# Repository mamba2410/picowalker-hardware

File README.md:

# picowalker hardware

This is the PCB hardware side of the [picowalker](https://github.com/mamba2410/picowalker) project.
The goal of the picowalker project is to create a new, modern equivalent to the Pokewalker distributed with the Pokemon HeartGold and SoulSilver games back in 2010.
Since those units are no longer sold and are getting harder and harder to obtain, creating a new version sounds like the easiest option. And the most fun.

The hardware is designed around the RP2350 chip. STM32U5 versions have been considered for longer battery life, but they're more expensive and I'm worried about availability (and the name "picowalker" wouldn't work!)

Software for this can be found in the [picowalker](https://github.com/mamba2410/picowalker/) and [picowalker-core](https://github.com/mamba2410/picowalker-core/) repos.

## Features

- RP2350A as the main microcontroller.
- 1.8" AMOLED screen DO0180FMST03, 448x368 resolution (running at 384x256 for 4x upscaling) driven by PIO'd QSPI (output only).
- Rechargeable lithum battery via USB-C using the BQ25628E PMIC.
- Larger form factor to accommodate larger screen and battery.
- Custom shell based on the original Pokewalker designed by Kamp.
- IrDA driven by PIO courtesy of Dmitry gr's PIO code.
- 64kB EEPROM using the M95512 chip (same as in the original walker).
- Code and extra image flash using 16MB W25Q128.
- Accelerometer with BMA400 (successor to the original Pokewalker's one).
- USB 1.1 connection for flexible communications.
- High accuracy, low power 32.768 kHz clock for more accurate timekeeping (100 PPM).

## Dependencies

- [KiCad](https://www.kicad.org/) V9.0+
- [KiKit](https://yaqwsx.github.io/KiKit/latest/installation/intro/) plugin to generate panels.
- Symbols, footprints and models are either in KiCad standard library or in a project library.

## Current state (updated 2025-12-19)

V0.4 has passed DRC checks. Will go through a few reviews so expect some tweaks.
Hoping that this will be the final version and, once validated, will be uplifted to V1.0.

Here's a render of the board.

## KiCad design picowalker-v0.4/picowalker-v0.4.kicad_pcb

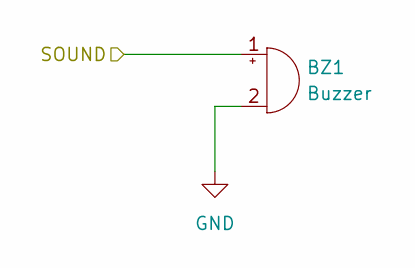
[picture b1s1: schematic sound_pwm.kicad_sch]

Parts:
BZ1: Buzzer; Huawei_P20_Speaker

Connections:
/SOUND: BZ1.1 (+); also elsewhere on the board
GND: BZ1.2 (-); also elsewhere on the board

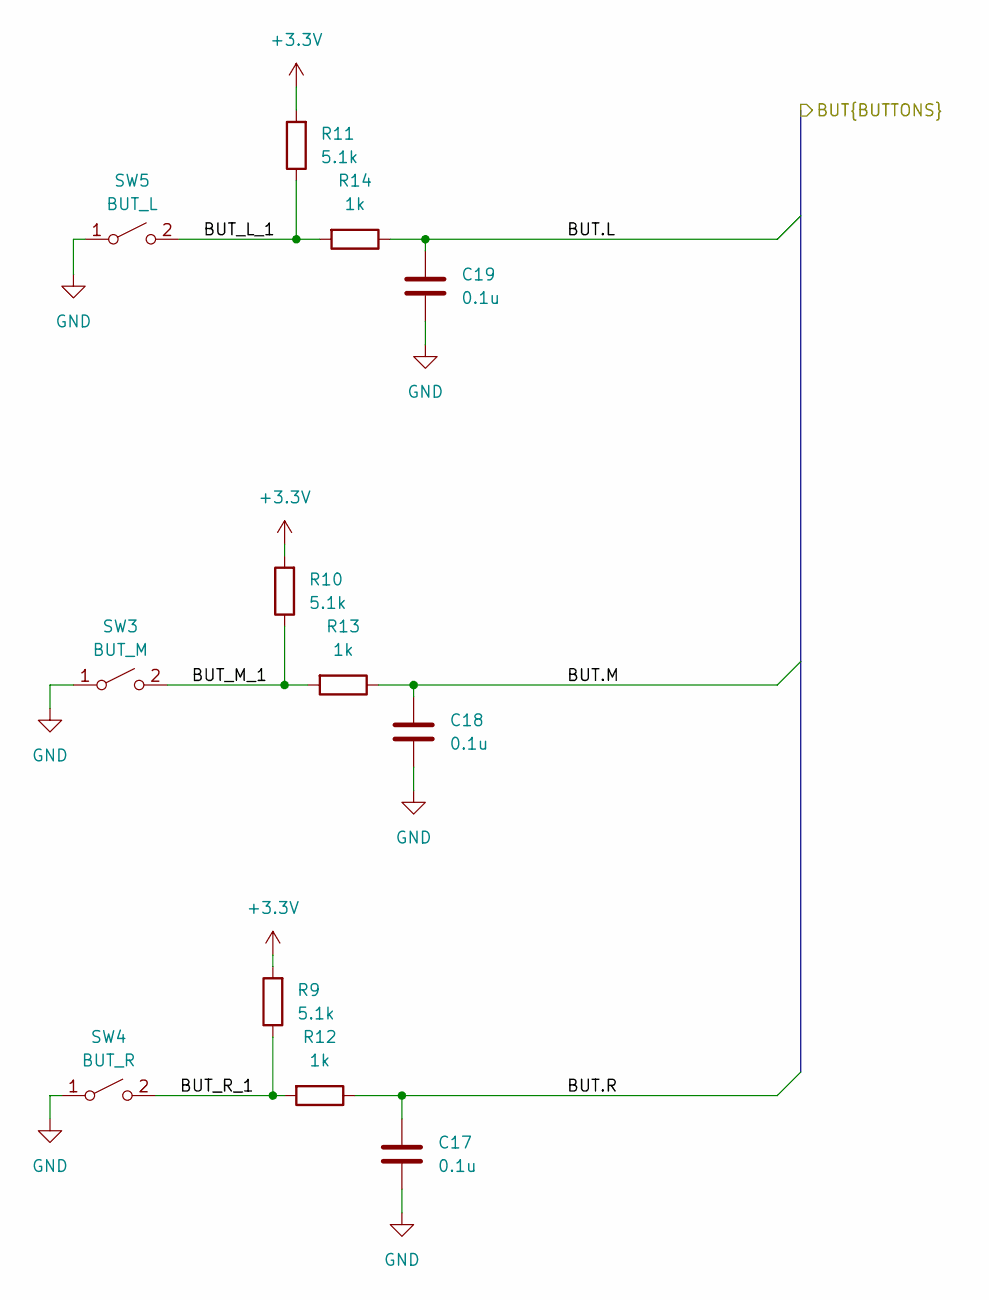
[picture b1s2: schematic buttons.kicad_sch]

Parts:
C17, C18, C19: 0.1u; C_0402_1005Metric
R9, R10, R11: 5.1k; R_0402_1005Metric
R12, R13, R14: 1k; R_0402_1005Metric
SW3: BUT_M; Button_membrane_4.2mm
SW4: BUT_R; Button_membrane_4.2mm
SW5: BUT_L; Button_membrane_4.2mm

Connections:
+3.3V: R9.2, R10.2, R11.2; also elsewhere on the board
/buttons/BUT.L: C19.1, R14.1; also elsewhere on the board
/buttons/BUT.M: C18.1, R13.1; also elsewhere on the board
/buttons/BUT.R: C17.1, R12.1; also elsewhere on the board
/buttons/BUT_L_1: R11.1, R14.2, SW5.2 (B)
/buttons/BUT_M_1: R10.1, R13.2, SW3.2 (B)
/buttons/BUT_R_1: R9.1, R12.2, SW4.2 (B)
GND: C17.2, C18.2, C19.2, SW3.1 (A), SW4.1 (A), SW5.1 (A); also elsewhere on the board

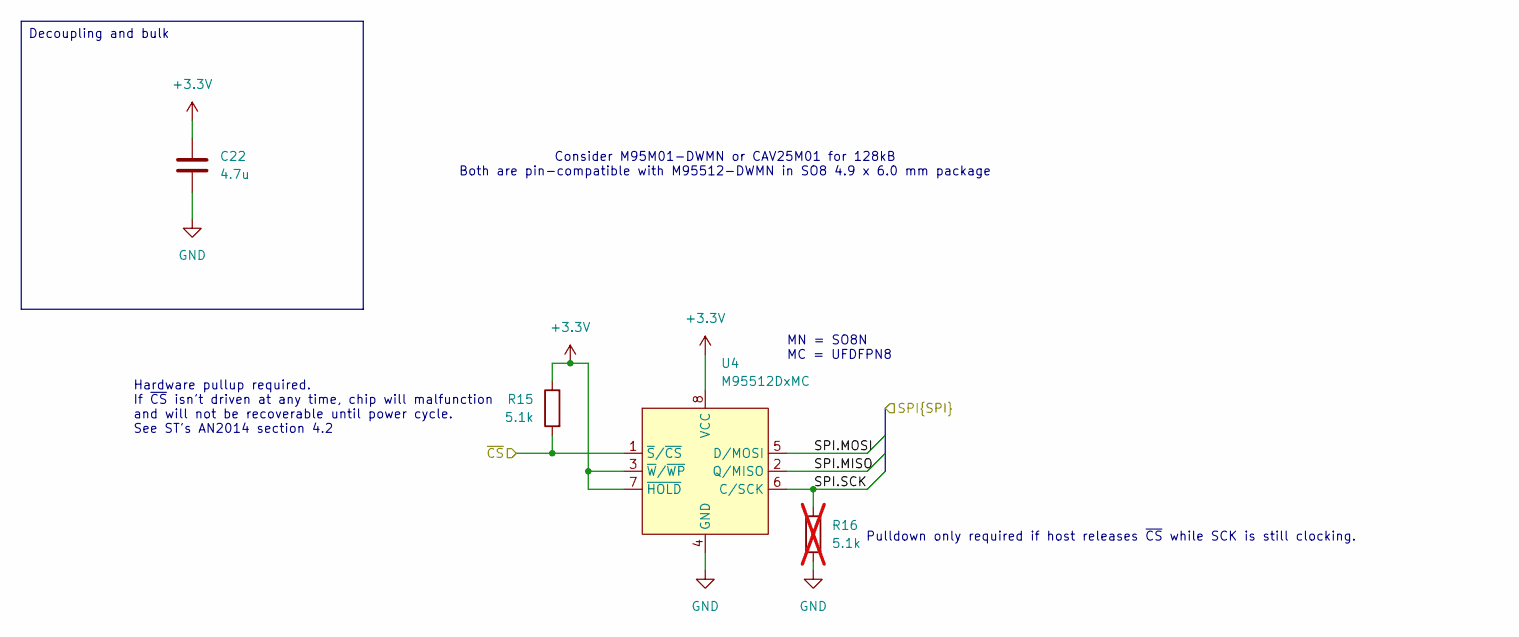
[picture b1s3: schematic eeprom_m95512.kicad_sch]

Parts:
C22: 4.7u; C_0402_1005Metric
R15: 5.1k; R_0402_1005Metric
R16: 5.1k; R_0402_1005Metric; not fitted
U4: M95512DxMC; UFDFPN8

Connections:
+3.3V: C22.1, R15.1, U4.3 (~W/~WP), U4.7 (~HOLD), U4.8 (VCC); also elsewhere on the board
/accel/SPI.MISO: U4.2 (Q/MISO); also elsewhere on the board
/accel/SPI.MOSI: U4.5 (D/MOSI); also elsewhere on the board
/accel/SPI.SCK: R16.1, U4.6 (C/SCK); also elsewhere on the board
/~EEPROM_CS: R15.2, U4.1 (~S/~CS); also elsewhere on the board
GND: C22.2, R16.2, U4.4 (GND), U4.9 (EPAD); also elsewhere on the board

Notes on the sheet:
MN = SO8N MC = UFDFPN8
Consider M95M01-DWMN or CAV25M01 for 128kB Both are pin-compatible with M95512-DWMN in SO8 4.9 x 6.0 mm package
Pulldown only required if host releases ~{CS} while SCK is still clocking.
Hardware pullup required. If ~{CS} isn't driven at any time, chip will malfunction and will not be recoverable until power cycle. See ST's AN2014 section 4.2
Decoupling and bulk

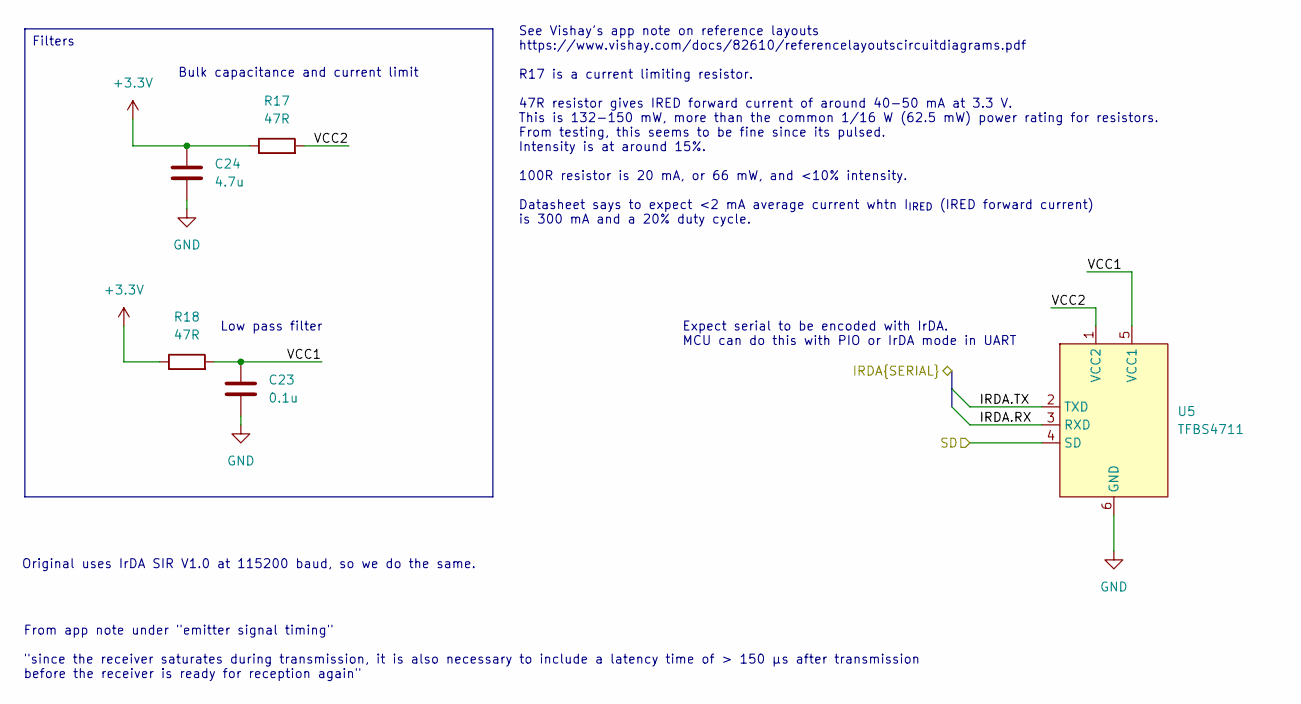
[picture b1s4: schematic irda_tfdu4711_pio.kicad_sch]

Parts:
C23: 0.1u; C_0402_1005Metric
C24: 4.7u; C_0402_1005Metric
R17, R18: 47R; R_0402_1005Metric
U5: TFBS4711; TFBS4711-TR

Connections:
+3.3V: C24.1, R17.1, R18.1; also elsewhere on the board
/IRDA_SD: U5.4 (SD); also elsewhere on the board
/irda/IRDA.RX: U5.3 (RXD); also elsewhere on the board
/irda/IRDA.TX: U5.2 (TXD); also elsewhere on the board
/irda/VCC1: C23.1, R18.2, U5.5 (VCC1)
/irda/VCC2: R17.2, U5.1 (VCC2)
GND: C23.2, C24.2, U5.6 (GND); also elsewhere on the board

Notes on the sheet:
Original uses IrDA SIR V1.0 at 115200 baud, so we do the same.
Expect serial to be encoded with IrDA. MCU can do this with PIO or IrDA mode in UART
Bulk capacitance and current limit
See Vishay's app note on reference layouts https://www.vishay.com/docs/82610/referencelayoutscircuitdiagrams.pdf R17 is a current limiting resistor. 47R resistor gives IRED forward current of around 40-50 mA at 3.3 V. This is 132-150 mW, more than the common 1/16 W (62.5 mW) power rating for resist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
From app note under "emitter signal timing" "since the receiver saturates during transmission, it is also necessary to include a latency time of > 150 μs after transmission before the receiver is ready for reception again"
Low pass filter
Filters

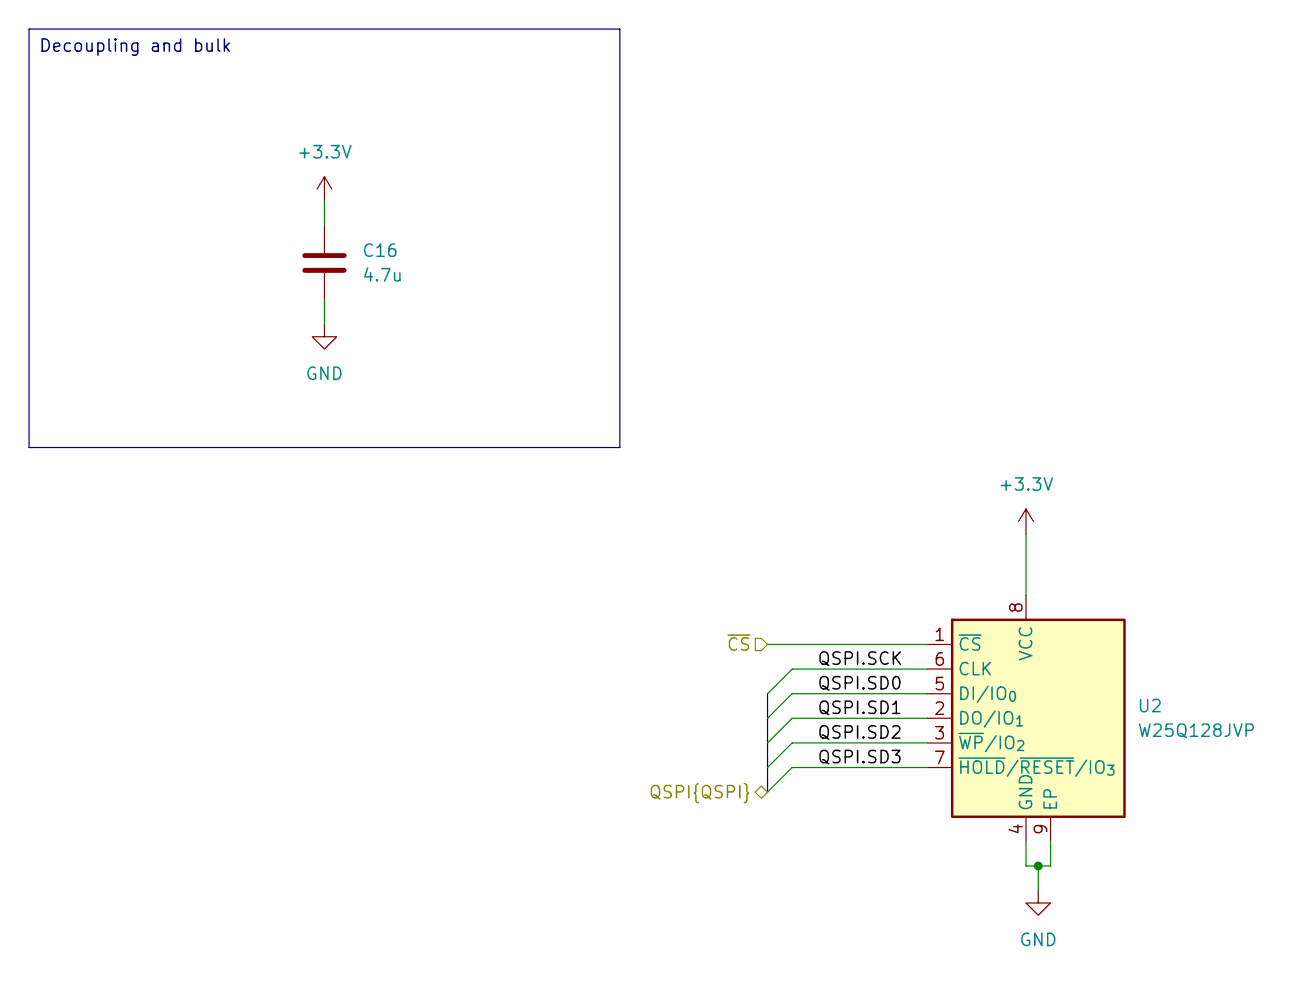
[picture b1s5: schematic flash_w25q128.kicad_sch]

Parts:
C16: 4.7u; C_0402_1005Metric
U2: W25Q128JVP; WSON-8-1EP_6x5mm_P1.27mm_EP3.4x4.3mm

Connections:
+3.3V: C16.1, U2.8 (VCC); also elsewhere on the board
/flash/QSPI.SCK: U2.6 (CLK); also elsewhere on the board
/flash/QSPI.SD0: U2.5 (DI/IO_{0}); also elsewhere on the board
/flash/QSPI.SD1: U2.2 (DO/IO_{1}); also elsewhere on the board
/flash/QSPI.SD2: U2.3 (~WP/IO_{2}); also elsewhere on the board
/flash/QSPI.SD3: U2.7 (~HOLD/~RESET/IO_{3}); also elsewhere on the board
/flash/~CS: U2.1 (~CS); also elsewhere on the board
GND: C16.2, U2.4 (GND), U2.9 (EP); also elsewhere on the board

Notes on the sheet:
Decoupling and bulk

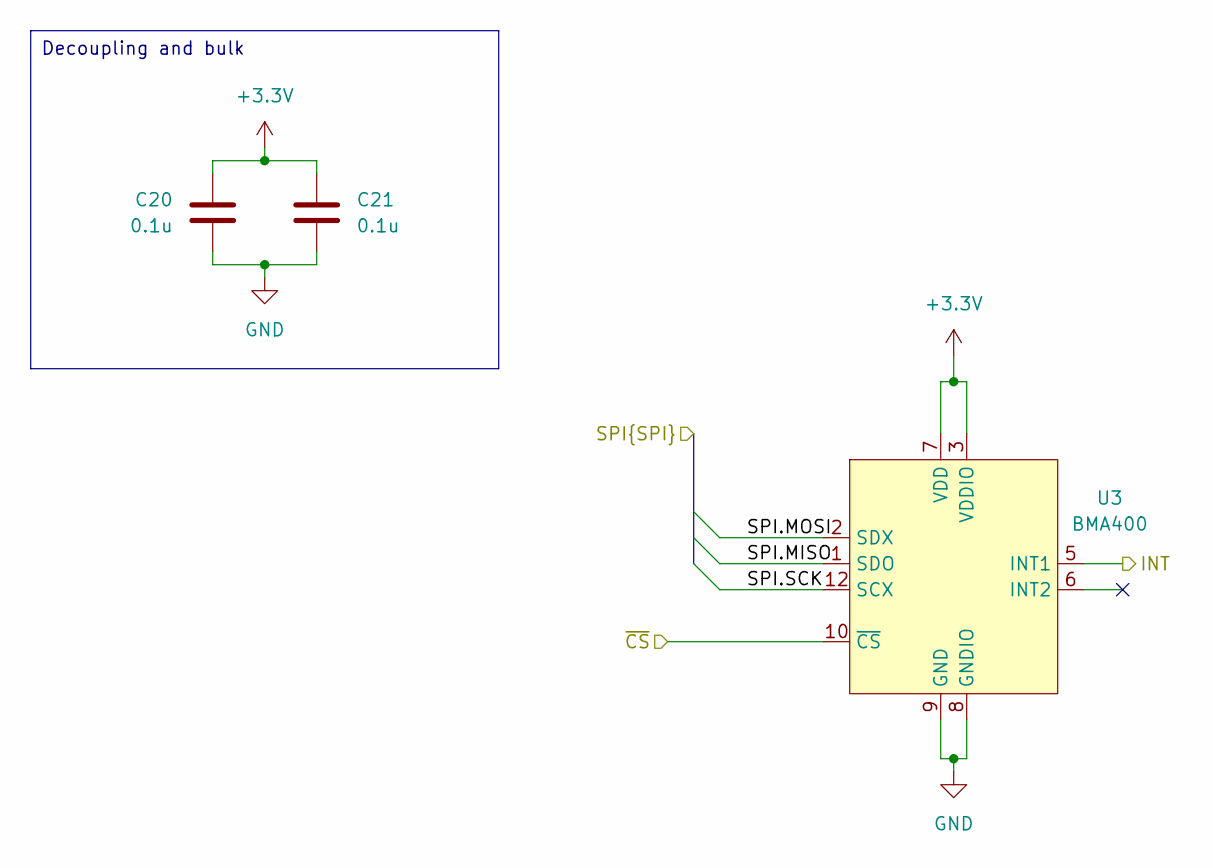
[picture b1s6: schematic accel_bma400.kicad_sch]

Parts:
C20, C21: 0.1u; C_0402_1005Metric
U3: BMA400; BOSCH_LGA-12_BMA400

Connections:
+3.3V: C20.1, C21.1, U3.3 (VDDIO), U3.7 (VDD); also elsewhere on the board
/ACCEL_INT: U3.5 (INT1); also elsewhere on the board
/accel/SPI.MISO: U3.1 (SDO); also elsewhere on the board
/accel/SPI.MOSI: U3.2 (SDX); also elsewhere on the board
/accel/SPI.SCK: U3.12 (SCX); also elsewhere on the board
/~ACCEL_CS: U3.10 (~CS); also elsewhere on the board
GND: C20.2, C21.2, U3.8 (GNDIO), U3.9 (GND); also elsewhere on the board

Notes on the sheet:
Decoupling and bulk

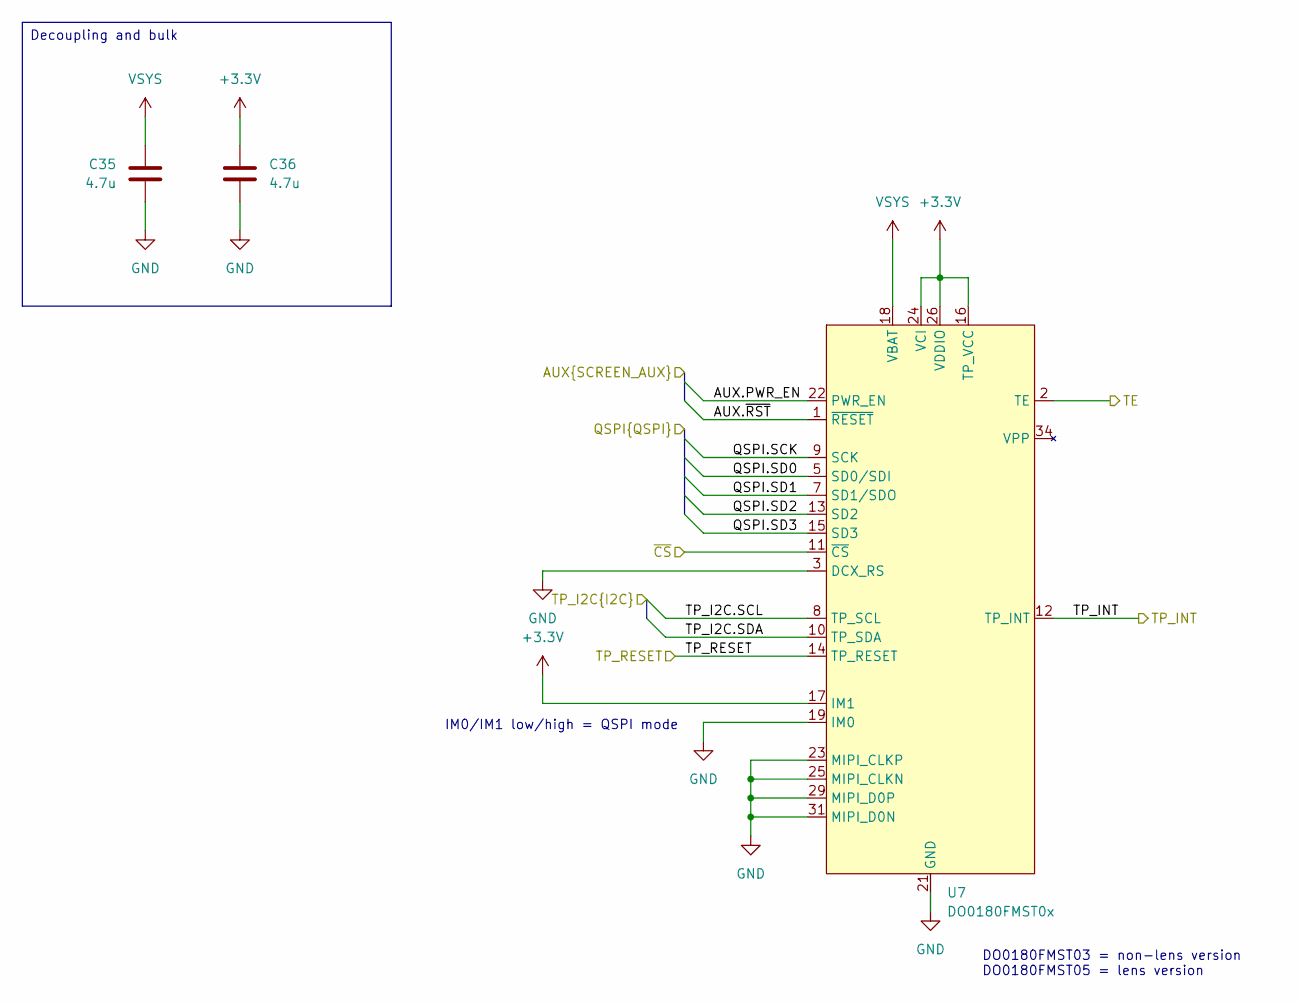
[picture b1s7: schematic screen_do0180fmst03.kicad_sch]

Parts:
C35, C36: 4.7u; C_0402_1005Metric
U7: DO0180FMST0x; AXE534127

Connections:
+3.3V: C36.2, U7.16 (TP_VCC), U7.17 (IM1), U7.24 (VCI), U7.26 (VDDIO); also elsewhere on the board
/TE: U7.2 (TE)
/TP_INT: U7.12 (TP_INT); also elsewhere on the board
/TP_RESET: U7.14 (TP_RESET); also elsewhere on the board
/mcu/I2C.SCL: U7.8 (TP_SCL); also elsewhere on the board
/mcu/I2C.SDA: U7.10 (TP_SDA); also elsewhere on the board
/mcu/SCREEN_AUX.PWR_EN: U7.22 (PWR_EN); also elsewhere on the board
/mcu/SCREEN_AUX.~RST: U7.1 (~RESET); also elsewhere on the board
/mcu/SCREEN_DATA.SCK: U7.9 (SCK); also elsewhere on the board
/mcu/SCREEN_DATA.SD0: U7.5 (SD0/SDI); also elsewhere on the board
/mcu/SCREEN_DATA.SD1: U7.7 (SD1/SDO); also elsewhere on the board
/mcu/SCREEN_DATA.SD2: U7.13 (SD2); also elsewhere on the board
/mcu/SCREEN_DATA.SD3: U7.15 (SD3); also elsewhere on the board
/~SCREEN_CS: U7.11 (~CS); also elsewhere on the board
GND: C35.2, C36.1, U7.3 (DCX_RS), U7.4 (GND), U7.19 (IM0), U7.21 (GND), U7.23 (MIPI_CLKP), U7.25 (MIPI_CLKN), U7.27 (GND), U7.28 (GND), U7.29 (MIPI_D0P), U7.31 (MIPI_D0N), U7.33 (GND); also elsewhere on the board
VSYS: C35.1, U7.18 (VBAT), U7.20 (VBAT); also elsewhere on the board

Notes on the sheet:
IM0/IM1 low/high = QSPI mode
DO0180FMST03 = non-lens version DO0180FMST05 = lens version
Decoupling and bulk

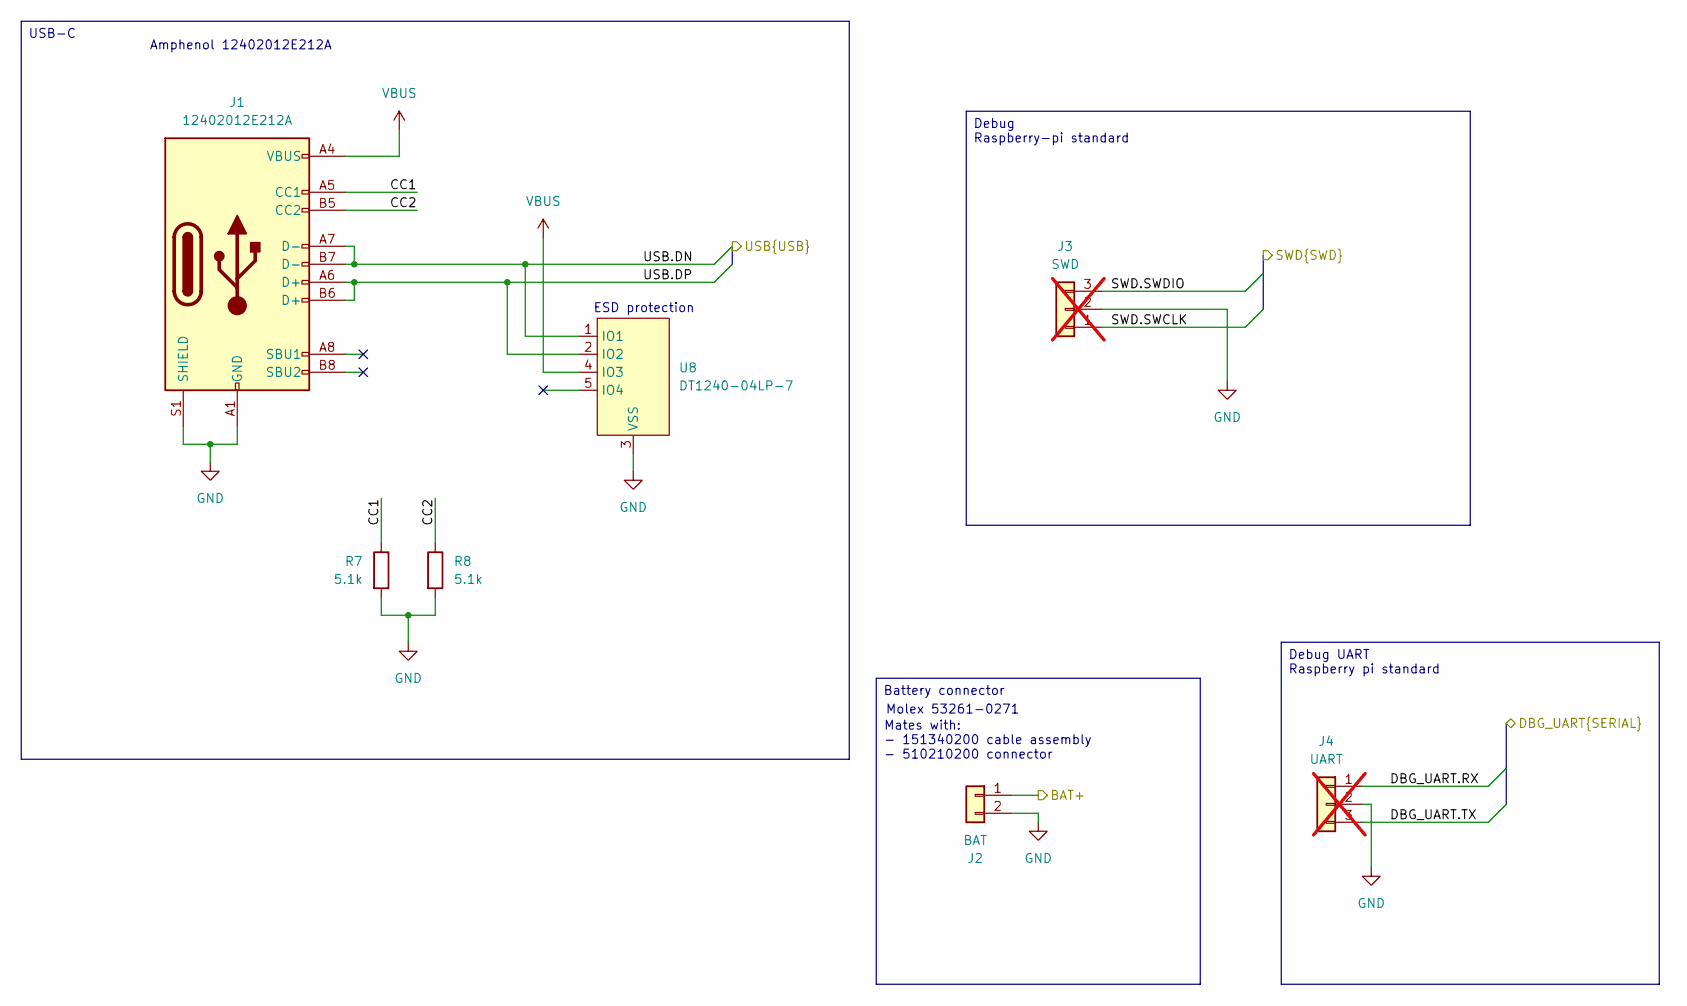
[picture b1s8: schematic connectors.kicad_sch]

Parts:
J1: 12402012E212A; USB_C_Receptacle_GCT_USB4105-xx-A_16P_TopMnt_Horizontal
J2: BAT; Molex_PicoBlade_53261-0271_1x02-1MP_P1.25mm_Horizontal
J3: SWD; JST_SH_SM03B-SRSS-TB_1x03-1MP_P1.00mm_Horizontal_wider; not fitted
J4: UART; JST_SH_SM03B-SRSS-TB_1x03-1MP_P1.00mm_Horizontal_wider; not fitted
R7, R8: 5.1k; R_0402_1005Metric
U8: DT1240-04LP-7; U-DFN2510-10_oneside

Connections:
/connectors/BAT+: J2.1; also elsewhere on the board
/connectors/CC1: J1.A5 (CC1), R7.1
/connectors/CC2: J1.B5 (CC2), R8.1
/connectors/DBG_UART.RX: J4.1; also elsewhere on the board
/connectors/DBG_UART.TX: J4.3; also elsewhere on the board
/connectors/SWD.SWCLK: J3.1; also elsewhere on the board
/connectors/SWD.SWDIO: J3.3; also elsewhere on the board
/connectors/USB.DN: J1.A7 (D-), J1.B7 (D-), U8.1 (IO1); also elsewhere on the board
/connectors/USB.DP: J1.A6 (D+), J1.B6 (D+), U8.2 (IO2); also elsewhere on the board
GND: J1.A1 (GND), J1.A12 (GND), J1.B1 (GND), J1.B12 (GND), J1.S1 (SHIELD), J2.2, J3.2, J4.2, R7.2, R8.2, U8.3 (VSS), U8.8 (VSS); also elsewhere on the board
VBUS: J1.A4 (VBUS), J1.A9 (VBUS), J1.B4 (VBUS), J1.B9 (VBUS), U8.4 (IO3); also elsewhere on the board

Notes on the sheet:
ESD protection
Mates with: - 151340200 cable assembly - 510210200 connector
Molex 53261-0271
Amphenol 12402012E212A
Battery connector
USB-C
Debug UART Raspberry pi standard
Debug Raspberry-pi standard

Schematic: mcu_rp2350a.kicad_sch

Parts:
C1, C37: 4.7u; C_0402_1005Metric_Smaller
C2, C4: 15p; C_0402_1005Metric
C3, C7: 4.7u; C_0402_1005Metric
C5, C6, C8, C9, C10, C11, C12, C13, C14: 0.1u; C_0402_1005Metric
L1: 3.3u; L_0805_2016Metric
R1: 47R; R_0402_1005Metric
R2, R3, R4: 1k; R_0402_1005Metric
R5, R6: 22R; R_0402_1005Metric
R23, R24: 5.1k; R_0402_1005Metric
SW1: ~{BOOT}; 435151014824
SW2: RUN; 435151014824
TP5: SDA; TestPoint_Pad_D1.0mm_Nosilk
TP12: 1V1; TestPoint_Pad_D1.0mm_Nosilk
TP13: SCL; TestPoint_Pad_D1.0mm_Nosilk
U1: RP2350A-QFN60; QFN-60-1EP_7x7mm_P0.4mm_EP3.4x3.4mm_ThermalVias
Y1: ABM8-272-T3; ABM8272T3

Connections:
+1.1V: C1.1, C5.1, C6.1, C7.1, L1.1, TP12.1 (1_1), U1.6 (DVDD), U1.23 (DVDD), U1.39 (DVDD), U1.50 (VREG_FB)
+3.3V: C8.1, C9.1, C10.1, C11.1, C12.1, C13.1, C14.1, C37.1, R1.1, R23.1, R24.1, U1.1 (IOVDD), U1.11 (IOVDD), U1.20 (IOVDD), U1.30 (IOVDD), U1.38 (IOVDD), U1.44 (ADC_AVDD), U1.45 (IOVDD), U1.49 (VREG_VIN), U1.53 (USB_OTP_VDD), U1.54 (QSPI_IOVDD); also elsewhere on the board
/ACCEL_INT: U1.35 (GPIO23); also elsewhere on the board
/IRDA_SD: U1.17 (GPIO13); also elsewhere on the board
/SOUND: U1.4 (GPIO2); also elsewhere on the board
/TP_INT: U1.27 (GPIO16); also elsewhere on the board
/TP_RESET: U1.28 (GPIO17); also elsewhere on the board
/accel/SPI.MISO: U1.32 (GPIO20); also elsewhere on the board
/accel/SPI.MOSI: U1.31 (GPIO19); also elsewhere on the board
/accel/SPI.SCK: U1.29 (GPIO18); also elsewhere on the board
/buttons/BUT.L: U1.37 (GPIO25); also elsewhere on the board
/buttons/BUT.M: U1.40 (GPIO26_ADC0); also elsewhere on the board
/buttons/BUT.R: U1.41 (GPIO27_ADC1); also elsewhere on the board
/connectors/DBG_UART.RX: U1.43 (GPIO29_ADC3); also elsewhere on the board
/connectors/DBG_UART.TX: U1.42 (GPIO28_ADC2); also elsewhere on the board
/connectors/SWD.SWCLK: U1.24 (SWCLK); also elsewhere on the board
/connectors/SWD.SWDIO: U1.25 (SWDIO); also elsewhere on the board
/connectors/USB.DN: R6.2; also elsewhere on the board
/connectors/USB.DP: R5.2; also elsewhere on the board
/flash/QSPI.SCK: U1.56 (QSPI_SCLK); also elsewhere on the board
/flash/QSPI.SD0: U1.57 (QSPI_SD0); also elsewhere on the board
/flash/QSPI.SD1: U1.59 (QSPI_SD1); also elsewhere on the board
/flash/QSPI.SD2: U1.58 (QSPI_SD2); also elsewhere on the board
/flash/QSPI.SD3: U1.55 (QSPI_SD3); also elsewhere on the board
/flash/~CS: R3.2, U1.60 (QSPI_SS); also elsewhere on the board
/irda/IRDA.RX: U1.18 (GPIO14); also elsewhere on the board
/irda/IRDA.TX: U1.19 (GPIO15); also elsewhere on the board
/mcu/I2C.SCL: R24.2, TP13.1 (1_1), U1.3 (GPIO1); also elsewhere on the board
/mcu/I2C.SDA: R23.2, TP5.1 (1_1), U1.2 (GPIO0); also elsewhere on the board
/mcu/RTC_CLK: U1.34 (GPIO22); also elsewhere on the board
/mcu/RUN: R2.2, U1.26 (RUN)
/mcu/SCREEN_AUX.PWR_EN: U1.8 (GPIO5); also elsewhere on the board
/mcu/SCREEN_AUX.~RST: U1.16 (GPIO12); also elsewhere on the board
/mcu/SCREEN_DATA.SCK: U1.10 (GPIO7); also elsewhere on the board
/mcu/SCREEN_DATA.SD0: U1.15 (GPIO11); also elsewhere on the board
/mcu/SCREEN_DATA.SD1: U1.14 (GPIO10); also elsewhere on the board
/mcu/SCREEN_DATA.SD2: U1.13 (GPIO9); also elsewhere on the board
/mcu/SCREEN_DATA.SD3: U1.12 (GPIO8); also elsewhere on the board
/mcu/SW_RUN_P: R2.1, SW2.2 (B)
/mcu/VREG_AVDD: C3.1, R1.2, U1.46 (VREG_AVDD)
/mcu/VREG_LX: L1.2, U1.48 (VREG_LX)
/mcu/XIN: C2.1, U1.21 (XIN), Y1.1
/mcu/XOUT: R4.2, U1.22 (XOUT)
/mcu/~BOOT: R3.1, SW1.2 (B)
/~ACCEL_CS: U1.33 (GPIO21); also elsewhere on the board
/~BAT_CE: U1.7 (GPIO4); also elsewhere on the board
/~BAT_INT: U1.5 (GPIO3); also elsewhere on the board
/~EEPROM_CS: U1.36 (GPIO24); also elsewhere on the board
/~SCREEN_CS: U1.9 (GPIO6); also elsewhere on the board
GND: C1.2, C2.2, C3.2, C4.2, C5.2, C6.2, C7.2, C8.2, C9.2, C10.2, C11.2, C12.2, C13.2, C14.2, C37.2, SW1.1 (A), SW1.3 (SHIELD), SW2.1 (A), SW2.3 (SHIELD), U1.47 (VREG_PGND), U1.61 (GND), Y1.2, Y1.4; also elsewhere on the board
unnamed: C4.1, R4.1, Y1.3
unnamed: R6.1, U1.51 (USB_DM)
unnamed: R5.1, U1.52 (USB_DP)

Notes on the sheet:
I2C0
"33R and 4.7u is adequate" -3 dB cutoff (1/2piRC) for 33R is 1026 Hz. 47R is 720 Hz.
4.7u specifically on pin 23
Ensure ground plane is >1.0 mm from surface
SPI0
PIO
Boot and reset buttons
Bus pullups
Decoupling and bulk
Test Points
12MHz Crystal
MCU 1.1V regulator

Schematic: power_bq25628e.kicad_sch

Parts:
C25, C26, C34: 4.7u; C_0402_1005Metric
C27, C28, C33: 10u; C_0603_1608Metric
C29, C30: 47u; C_0805_2012Metric
C31: 47n; C_0402_1005Metric
C32: 0.1u; C_0402_1005Metric
D1: ~{STAT}; LED_0402_1005Metric
L2: 1.1u; L_0603_1608Metric
L3: 2.2u; L_0805_2012Metric
R19, R21: 5.1k; R_0402_1005Metric
R20: 30k; R_0603_1608Metric
R22: 1k; R_0402_1005Metric
TH1: 10k; R_0402_1005Metric
TP1: ~{PG}; TestPoint_Pad_D1.0mm_Nosilk
TP2: ~{QON}; TestPoint_Pad_D1.0mm_Nosilk
U6: BQ25628ERYKR
U9: RT6150B-33GQW; SON50P250X250X80-11N-D

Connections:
+3.3V: C30.1, R22.1, U9.1 (VOUT), U9.10 (FB); also elsewhere on the board
/connectors/BAT+: C25.1, U6.8 (BAT+); also elsewhere on the board
/mcu/I2C.SCL: U6.13 (SCL); also elsewhere on the board
/mcu/I2C.SDA: U6.12 (SDA); also elsewhere on the board
/power/PMID: C32.1, C33.1, U6.17 (PMID)
/power/SW: C31.1, L2.1, U6.16 (SW)
/power/TS: R19.2, R20.1, TH1.1, U6.6 (TS)
/power/TS_BIAS: R19.1, U6.5 (TS_BIAS)
/power/~PG: TP1.1 (1_1), U6.3 (~PG)
/power/~QON: TP2.1 (1_1), U6.7 (~QON)
/power/~STAT: D1.1 (K), U6.10 (STAT)
/~BAT_CE: U6.14 (~CE); also elsewhere on the board
/~BAT_INT: U6.11 (~INT); also elsewhere on the board
GND: C25.2, C26.2, C27.2, C28.2, C29.2, C30.2, C32.2, C33.2, C34.2, R20.2, R21.2, TH1.2, U6.15 (GND), U9.3 (GND), U9.7 (PS), U9.9 (GND), U9.11 (GND_PAD); also elsewhere on the board
unnamed: D1.2 (A), R22.2
unnamed: C31.2, U6.1 (BTST)
unnamed: R21.1, U6.4 (ILIM)
unnamed: C34.1, U6.2 (REGN)
unnamed: L3.1, U9.4 (LX1)
unnamed: L3.2, U9.2 (LX2)
VBUS: C26.1, U6.18 (VBUS); also elsewhere on the board
VSYS: C27.1, C28.1, C29.1, L2.2, U6.9 (SYS), U9.5 (VIN), U9.6 (EN), U9.8 (VINA); also elsewhere on the board

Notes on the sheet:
Datasheet recommends: CVBUS > 1u CPMID > 10u CSYS > 20u CBAT > 10u
I_ILIM = K_ILIM/R_ILIM K_ILIM = 2500 +/-250 5.1k = 490 mA
I think stuck at 47n. Its a bootstrap so keep to recommended.
Datasheet: 5.32k
Datasheet: 30.1k
PS low = power save mode (unknown switching method) PS high = PWM mode @ 1 MHz
Thermistor
PMIC battery charger with power path
Indicator LEDs
Unused pins
Decoupling, smoothing and bulk
3.3V switching regulator Basically taken from pico 2 datasheet/schematic

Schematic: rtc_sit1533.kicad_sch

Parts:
TP3: 32k; TestPoint_Pad_D1.0mm_Nosilk
TP4: GND; TestPoint_Pad_D1.0mm_Nosilk
Y2: SIT1533AI-H4-DCC-32.768E; SIT1533AIH4DCC32768E; Mouser Part Number 788-1533AIH4DCC32.76

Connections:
+3.3V: Y2.4 (VDD); also elsewhere on the board
/mcu/RTC_CLK: TP3.1 (1_1), Y2.3 (CLK_OUT); also elsewhere on the board
GND: TP4.1 (1_1), Y2.2 (GND); also elsewhere on the board

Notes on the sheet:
32768 Hz 75 ppm stability from -10 C to +70 C 20 ppm tolerance 1 ppm aging (1 year) = ~100 ppm = +/-4 Hz = ~ 9 seconds/day max drift

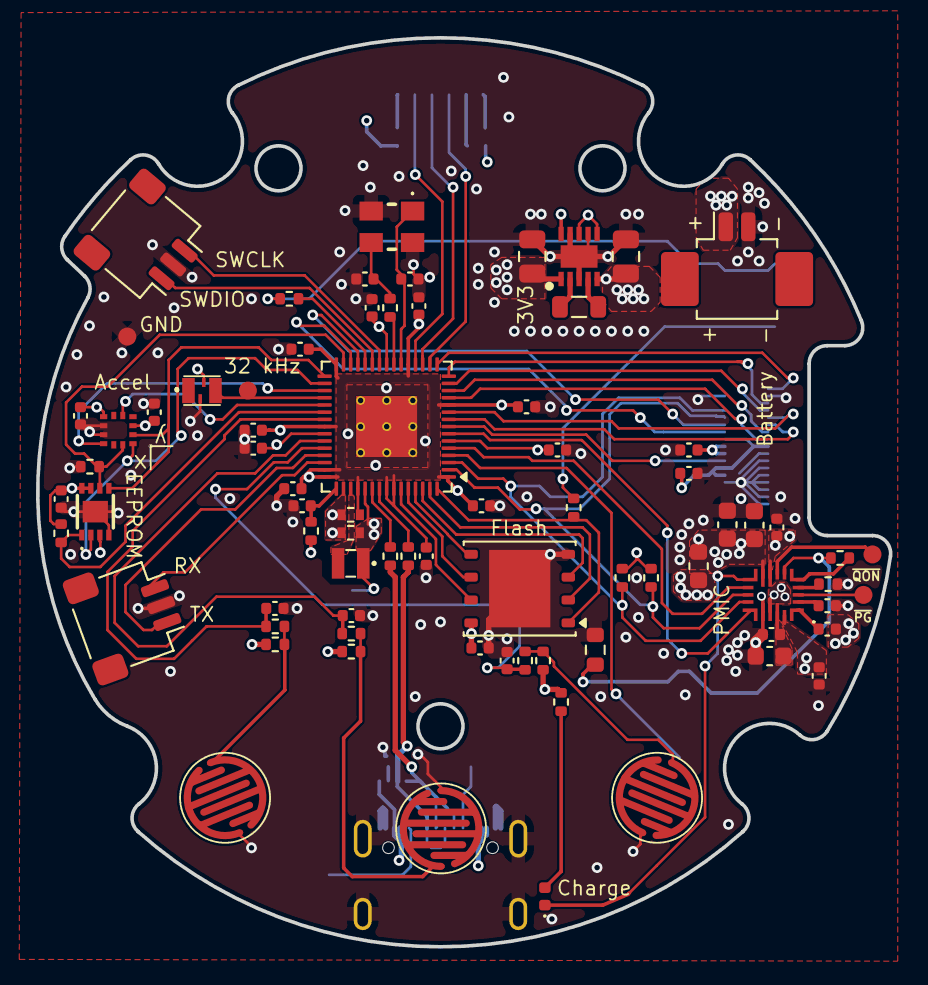
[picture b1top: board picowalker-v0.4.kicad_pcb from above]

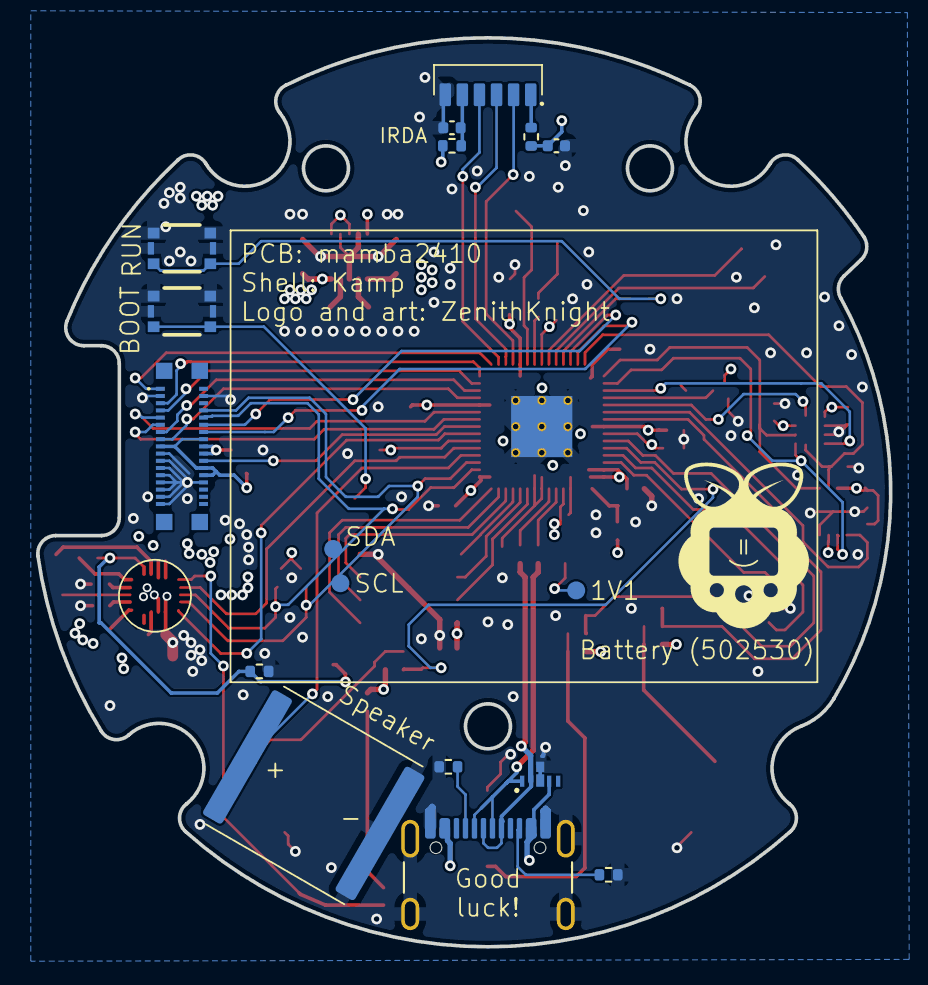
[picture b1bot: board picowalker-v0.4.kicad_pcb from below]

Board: 4 copper layers, 47.4 x 50.5 mm, 93 parts (17 on the bottom side), 76 nets.

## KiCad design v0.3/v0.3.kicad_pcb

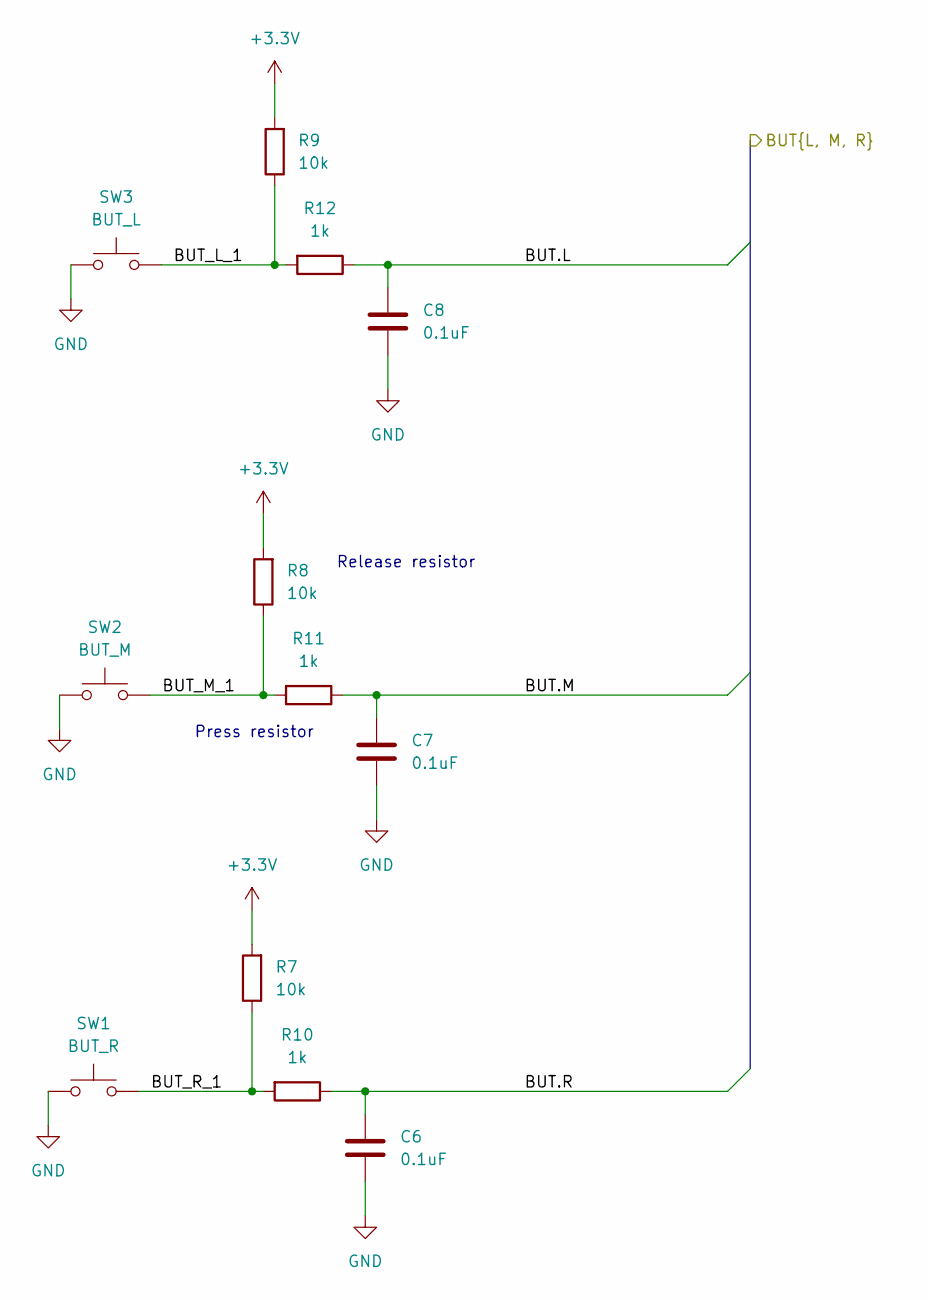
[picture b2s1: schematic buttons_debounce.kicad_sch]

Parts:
C6, C7, C8: 0.1uF; C_0402_1005Metric
R7, R8, R9: 10k; R_0402_1005Metric
R10, R11, R12: 1k; R_0402_1005Metric
SW1: BUT_R; Button_membrane_5mm
SW2: BUT_M; Button_membrane_5mm
SW3: BUT_L; Button_membrane_5mm

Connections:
+3.3V: R7.2, R8.2, R9.2; also elsewhere on the board
/buttons/BUT.L: C8.1, R12.1; also elsewhere on the board
/buttons/BUT.M: C7.1, R11.1; also elsewhere on the board
/buttons/BUT.R: C6.1, R10.1; also elsewhere on the board
/buttons/BUT_L_1: R9.1, R12.2, SW3.2
/buttons/BUT_M_1: R8.1, R11.2, SW2.2
/buttons/BUT_R_1: R7.1, R10.2, SW1.2
GND: C6.2, C7.2, C8.2, SW1.1, SW2.1, SW3.1; also elsewhere on the board

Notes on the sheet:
Press resistor
Release resistor

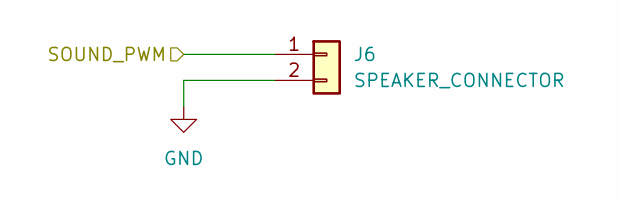
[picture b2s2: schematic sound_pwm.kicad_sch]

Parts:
J6: SPEAKER_CONNECTOR; R_0603_1608Metric

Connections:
/mcu/SOUND_PWM: J6.1; also elsewhere on the board
GND: J6.2; also elsewhere on the board
